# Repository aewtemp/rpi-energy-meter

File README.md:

# ----- W.I.P -----
# Raspberry-Pi Energy Meter

This Project is a combination of custom Hardware and Software, that will allow you to monitor your unique power situation in real time.

This project is derived from and inspired by the resources located at https://github.com/David00/rpi-power-monitor and https://learn.openenergymonitor.org.

## What does it do?
This code accompanies DIY circuitry that supports monitoring of up to 3 Phases with 6 current transformers each. The individual readings are then used in calculations to provide real data on consumption and generation, including the following key metrics:
* Voltage of every pahse
* Current on up to 6 channels per phase
* Power Factor
* Harmonics inspection through a built in snapshot/plotting mechanism.

The code takes thousands of samples per second, corrects for phase errors in the measurements, calculates the instantaneous power for the tens of thousands of sampled points, and uses the instantaneous power calculations to determine real power, apparent power, and power factor. This means the project is able to monitor any type of load, including reactive, capacitive, and resisitve loads.

## Where can I get it?
The whole Project is open sourced. You can order your PCBs via the Files provided in the [PCB Folder](PCB).  
You'll also find a [README](PCB/README.md) there which will provide more useful information.

## Installation & Documentation

### Ordering
#### Components for the PCB
Please take the respective components and their needed quantities from the [CSV](PCB/Production/RPiWattMeterHatv3.csv) inside the [PCB](PCB) folder.
#### The PCB
Just send the gerber files to the PCB Manufacturer of your choice.
If you provide the components file and the locations with the gerber files, you might be able to get the PCB nearly fully assembled.

### Preparing the Pi
#### System-Setup
You'll need a raspberry pi 3B with an installed operating system on it.
This has to be a 32-bit version, because the overlay file needed for the SPI-bus configuration won't work on 64-bit operating systems.
Currently supported operating systems are Debian (>11) and Ubuntu (>20.04)

* Copy the [overlay file (system_overlay/spi0-3cs-overlay.dtbo)](sytem_overlay/spi0-3cs-overlay.dtbo) into /boot/overlays  
* reboot

#### Installing the necessary software

### Installation and Configuration
#### Installation into the Cabinet
You will need 4 additional components to get the rpi-energy-meter up and running.
1. A DIN rail mountable power supply  
I had chosen this one: [MeanWell HDR-15-5](https://meanwell-ps.com/products/hdr-15-5)
2. 3 x fuse blocks, rated for 250V  
I had chosen this one: [XCELL UK5](https://www.uxcell.com/din-rail-mount-fuse-holder-terminal-blocks-screw-type-black-uk5-pack-p-1946790.html)
3. 3 x glass fuse, rated for 250V and 250mA  
I had chosen this one: [FUSE GLASS](https://www.digikey.de/en/products/detail/bel-fuse-inc/5HT-250-R/4439452)
4. Wires  
Ideally one would use black for the 230V live wires from and to the fuse holders, blue ones for the neutrals and red/black wires for the current transformer wires.  
The cross sections of the wires is:
    1. 230V/Neutal
        1. To the fuse blocks = 1.5mm² (15 AWG)
        1. From the fuse blocks = 0.5mm² (20 AWG)
        1. From the board (Neutral) = 0.5mm² (20 AWG)
    2. Current transformers
        1. Should be 0.5mm² or less (>= 20 AWG)

Select where you want your Voltage to be taken of for measurement. You'll have to select 3 sources, one for each phase.  
Connect wires from these points up to the fuse holders. From there you'll connect wires to the PCB - right where the imprint "DANGER HIGH VOLTAGE" is located.  
With the socket located at the bottom, left is phase 1, middle two are phase 2 and the right ones are phase 3.  
The Sequence is **N-L1-N-L2-N-L3**

#### Measuring required references
This step consists of some measurements which have to be taken in the cabinet and on the PCB. On the PCB are therefore some exposed through holes where you can take measurements from.

**!! BE CAREFUL WHEN TAKING MEASUREMENTS ON LIVE COMPONENTS !!**  

The following measurements have to be done:
* Voltages DC
    * 3.3V reference -> Exposed pads right next to the MCP3008 chips  
    Write down that value, it's needed later for the config.toml
    * Bias_V -> Exposed pads right above the Transformers on the PCB  
    Should be half of the reference Voltage
* Voltage AC
    * L{1,2,3}TRANS -> Exposed pads right next to the MCP3008 chips  
    Should read something from 2.0V to 2.2V RMS

#### Configuring the Energy-Meter

### Setting up a systemd service
* copy the [example systemd service file](examples/systemd/rpi-energy-meter.service) to /etc/systemd/system  
* modify the contents of /etc/systemd/systemd/rpi-energy-meter.service corresponding to your setup  
Most often you will need to adjust paths accordingly

### Expected results
#### Debug mode
The html charts generated by debug mode should look something like this  
[Phase 1](examples/debug/Phase_1.html?raw=true)  
[Phase 2](examples/debug/Phase_2.html?raw=true)  
[Phase 3](examples/debug/Phase_3.html?raw=true)

## Contributing

## Credits

---

## If you like what I did, you are welcome to leave me some support

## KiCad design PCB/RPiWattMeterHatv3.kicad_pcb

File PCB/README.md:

# ----- W.I.P -----
# Raspberry-Pi Energy Meter HAT

## What does it do?
This PCB is designed for measuring electrical current across three phases, with 6 individual channels per phase. Each channel represents a separate current path and uses current transformers (CTs) for sensing. The board uses 22 Ohm burden resistors for each CT channel.

Additionally, the board incorporates transformers to step down the mains voltage to a measurable level for voltage monitoring. **Caution:** This board operates with potentially dangerous voltages. There is **no touch protection**, and **improper handling may result in electric shock**.

This is a DIY project and comes with **no warranty or guarantee** of safety or performance. Use at your own risk.  
I personally have this setup running now for 2 years.

## Pictures of running setup

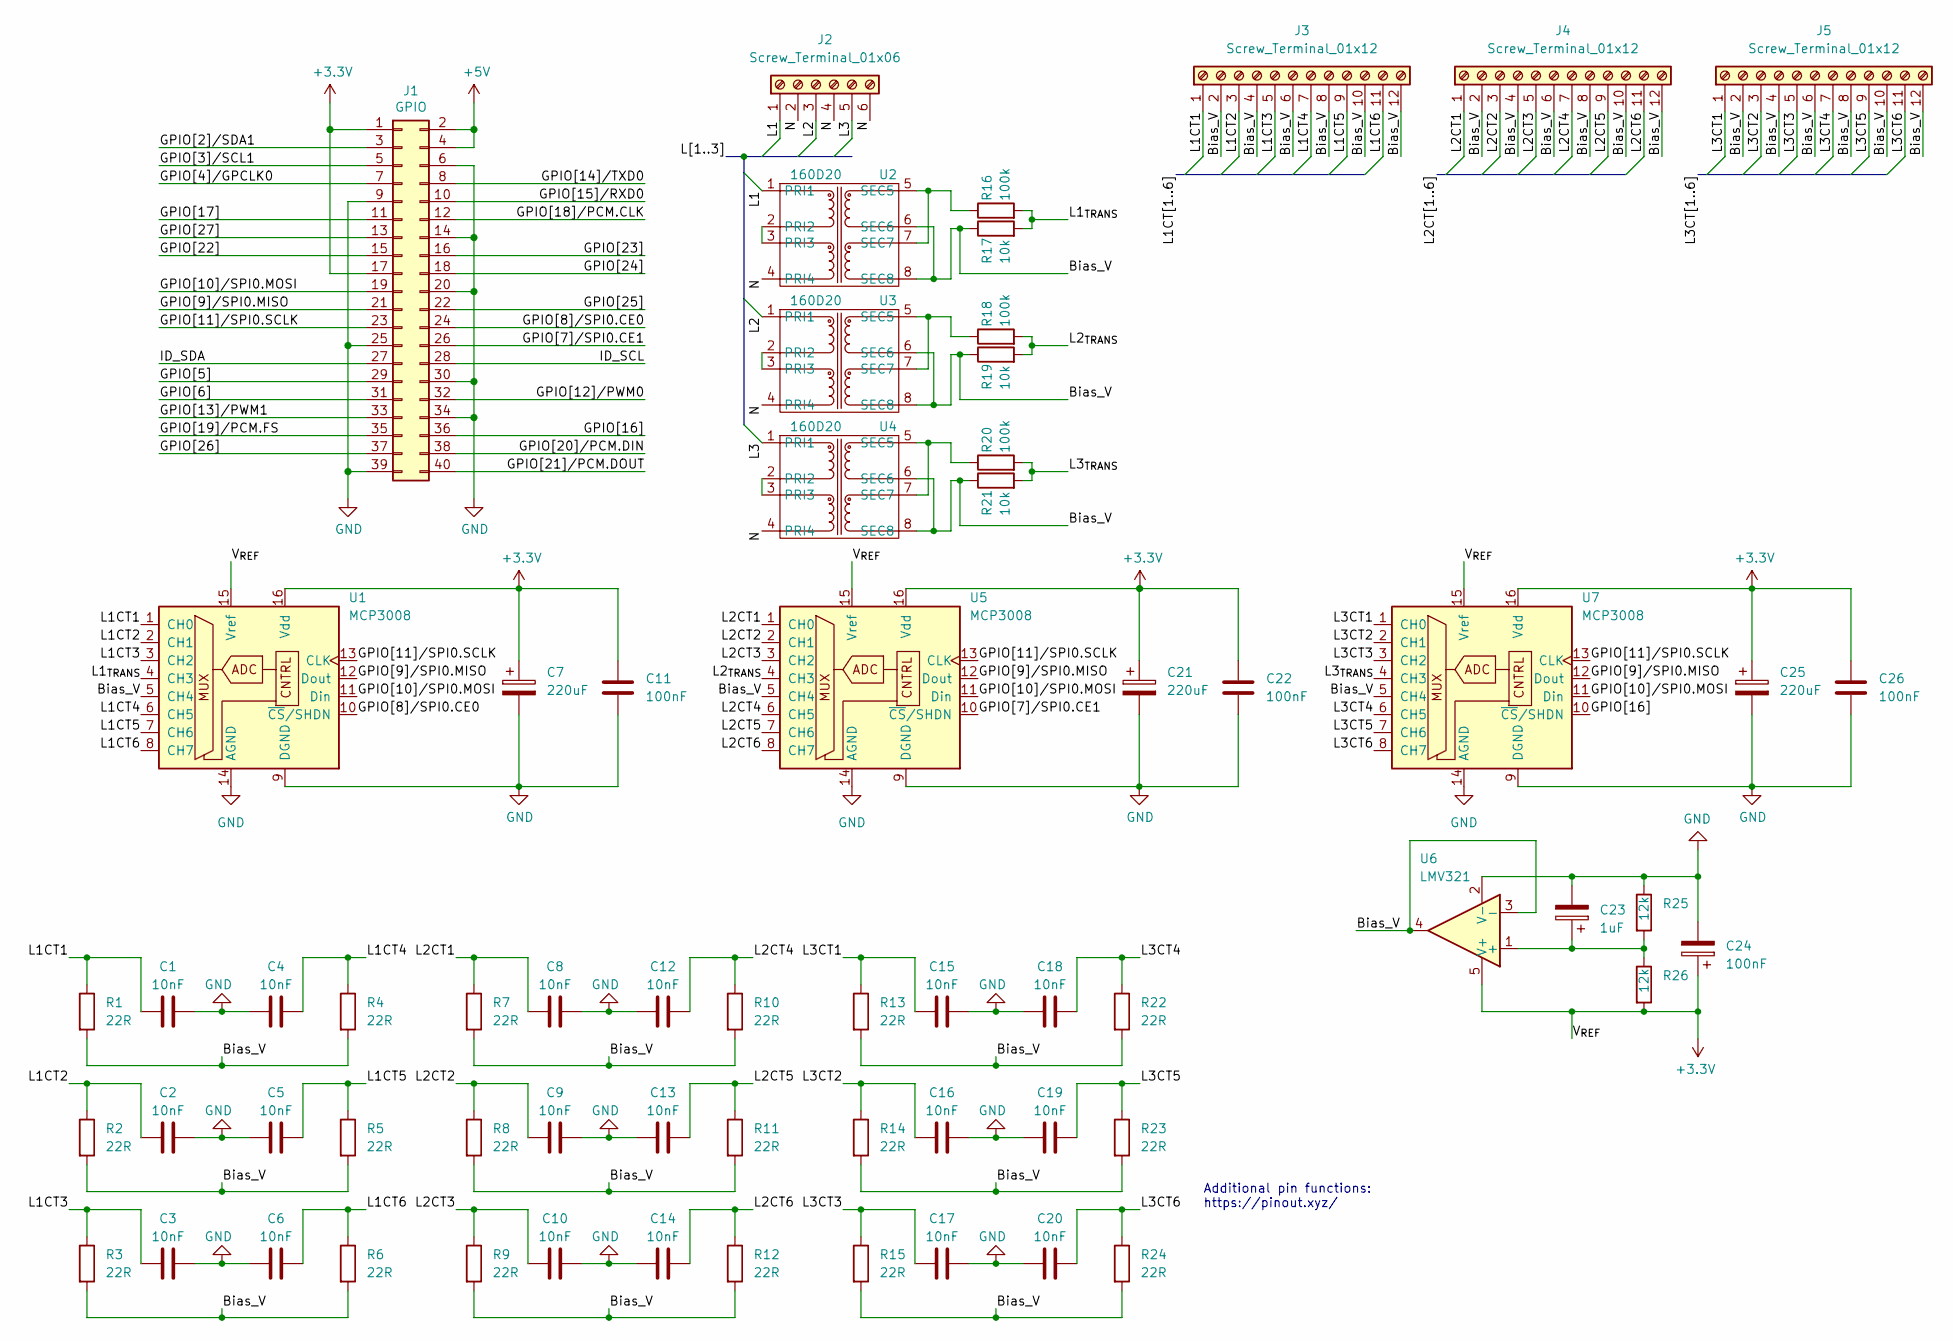
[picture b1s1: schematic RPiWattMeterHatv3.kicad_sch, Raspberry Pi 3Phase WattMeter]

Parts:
C1, C2, C3, C4, C5, C6, C8, C9, C10, C12, C13, C14, C15, C16, C17, C18, C19, C20: 10nF; C_1206_3216Metric_Pad1.33x1.80mm_HandSolder
C7, C21, C25: 220uF; CP_EIA-3216-12_Kemet-S_Pad1.58x1.35mm_HandSolder
C11, C22, C26: 100nF; C_1206_3216Metric_Pad1.33x1.80mm_HandSolder
C23: 1uF; C_1206_3216Metric_Pad1.33x1.80mm_HandSolder
C24: 100nF; CP_EIA-3216-12_Kemet-S_Pad1.58x1.35mm_HandSolder
J1: GPIO; PinSocket_2x20_P2.54mm_Vertical
J2: Screw_Terminal_01x06; PhoenixContact_1891108
J3, J4, J5: Screw_Terminal_01x12; PhoenixContact_PTSA 0,5_12-2,5-F
R1, R2, R3, R4, R5, R6, R7, R8, R9, R10, R11, R12, R13, R14, R15, R22, R23, R24: 22R; R_1206_3216Metric_Pad1.30x1.75mm_HandSolder
R16, R18, R20: 100k; R_1206_3216Metric_Pad1.30x1.75mm_HandSolder
R17, R19, R21: 10k; R_1206_3216Metric_Pad1.30x1.75mm_HandSolder
R25, R26: 12k; R_1206_3216Metric_Pad1.30x1.75mm_HandSolder
U1, U5, U7: MCP3008; DIP-16_W7.62mm_Socket
U2, U3, U4: 160D20; Hammond_160D20
U6: LMV321; SOT-23-5

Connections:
+3.3V: C7.1, C11.1, C21.1, C22.1, C24.1, C25.1, C26.1, J1.1, J1.17, R26.2, U1.15 (Vref), U1.16 (Vdd), U5.15 (Vref), U5.16 (Vdd), U6.5 (V+), U7.15 (Vref), U7.16 (Vdd)
+5V: J1.2, J1.4
/Bias_V: J3.2, J3.4, J3.6, J3.8, J3.10, J3.12, J4.2, J4.4, J4.6, J4.8, J4.10, J4.12, J5.2, J5.4, J5.6, J5.8, J5.10, J5.12, R1.2, R2.2, R3.2, R4.2, R5.2, R6.2, R7.2, R8.2, R9.2, R10.2, R11.2, R12.2, R13.2, R14.2, R15.2, R17.1, R19.1, R21.1, R22.2, R23.2, R24.2, U1.5 (CH4), U2.6 (SEC6), U2.8 (SEC8), U3.6 (SEC6), U3.8 (SEC8), U4.6 (SEC6), U4.8 (SEC8), U5.5 (CH4), U6.3 (-), U6.4, U7.5 (CH4)
/GPIO[2]/SDA1: J1.3
/GPIO[3]/SCL1: J1.5
/GPIO[4]/GPCLK0: J1.7
/GPIO[5]: J1.29
/GPIO[6]: J1.31
/GPIO[7]/SPI0.CE1: J1.26, U5.10 (~CS/SHDN)
/GPIO[8]/SPI0.CE0: J1.24, U1.10 (~CS/SHDN)
/GPIO[9]/SPI0.MISO: J1.21, U1.12 (Dout), U5.12 (Dout), U7.12 (Dout)
/GPIO[10]/SPI0.MOSI: J1.19, U1.11 (Din), U5.11 (Din), U7.11 (Din)
/GPIO[11]/SPI0.SCLK: J1.23, U1.13 (CLK), U5.13 (CLK), U7.13 (CLK)
/GPIO[12]/PWM0: J1.32
/GPIO[13]/PWM1: J1.33
/GPIO[14]/TXD0: J1.8
/GPIO[15]/RXD0: J1.10
/GPIO[16]: J1.36, U7.10 (~CS/SHDN)
/GPIO[17]: J1.11
/GPIO[18]/PCM.CLK: J1.12
/GPIO[19]/PCM.FS: J1.35
/GPIO[20]/PCM.DIN: J1.38
/GPIO[21]/PCM.DOUT: J1.40
/GPIO[22]: J1.15
/GPIO[23]: J1.16
/GPIO[24]: J1.18
/GPIO[25]: J1.22
/GPIO[26]: J1.37
/GPIO[27]: J1.13
/ID_SCL: J1.28
/ID_SDA: J1.27
/L1: J2.1, U2.1 (PRI1)
/L1CT1: C1.2, J3.1, R1.1, U1.1 (CH0)
/L1CT2: C2.2, J3.3, R2.1, U1.2 (CH1)
/L1CT3: C3.2, J3.5, R3.1, U1.3 (CH2)
/L1CT4: C4.1, J3.7, R4.1, U1.6 (CH5)
/L1CT5: C5.1, J3.9, R5.1, U1.7 (CH6)
/L1CT6: C6.1, J3.11, R6.1, U1.8 (CH7)
/L1_{TRANS}: R16.2, R17.2, U1.4 (CH3)
/L2: J2.3, U3.1 (PRI1)
/L2CT1: C8.2, J4.1, R7.1, U5.1 (CH0)
/L2CT2: C9.2, J4.3, R8.1, U5.2 (CH1)
/L2CT3: C10.2, J4.5, R9.1, U5.3 (CH2)
/L2CT4: C12.1, J4.7, R10.1, U5.6 (CH5)
/L2CT5: C13.1, J4.9, R11.1, U5.7 (CH6)
/L2CT6: C14.1, J4.11, R12.1, U5.8 (CH7)
/L2_{TRANS}: R18.2, R19.2, U5.4 (CH3)
/L3: J2.5, U4.1 (PRI1)
/L3CT1: C15.2, J5.1, R13.1, U7.1 (CH0)
/L3CT2: C16.2, J5.3, R14.1, U7.2 (CH1)
/L3CT3: C17.2, J5.5, R15.1, U7.3 (CH2)
/L3CT4: C18.1, J5.7, R22.1, U7.6 (CH5)
/L3CT5: C19.1, J5.9, R23.1, U7.7 (CH6)
/L3CT6: C20.1, J5.11, R24.1, U7.8 (CH7)
/L3_{TRANS}: R20.2, R21.2, U7.4 (CH3)
/N: J2.2, J2.4, J2.6, U2.4 (PRI4), U3.4 (PRI4), U4.4 (PRI4)
GND: C1.1, C2.1, C3.1, C4.2, C5.2, C6.2, C7.2, C8.1, C9.1, C10.1, C11.2, C12.2, C13.2, C14.2, C15.1, C16.1, C17.1, C18.2, C19.2, C20.2, C21.2, C22.2, C23.2, C24.2, C25.2, C26.2, J1.6, J1.9, J1.14, J1.20, J1.25, J1.30, J1.34, J1.39, R25.1, U1.9 (DGND), U1.14 (AGND), U5.9 (DGND), U5.14 (AGND), U6.2 (V-), U7.9 (DGND), U7.14 (AGND)
unnamed: C23.1, R25.2, R26.1, U6.1 (+)
unnamed: R16.1, U2.5 (SEC5), U2.7 (SEC7)
unnamed: R18.1, U3.5 (SEC5), U3.7 (SEC7)
unnamed: R20.1, U4.5 (SEC5), U4.7 (SEC7)
unnamed: U2.2 (PRI2), U2.3 (PRI3)
unnamed: U3.2 (PRI2), U3.3 (PRI3)
unnamed: U4.2 (PRI2), U4.3 (PRI3)

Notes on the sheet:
Additional pin functions: https://pinout.xyz/

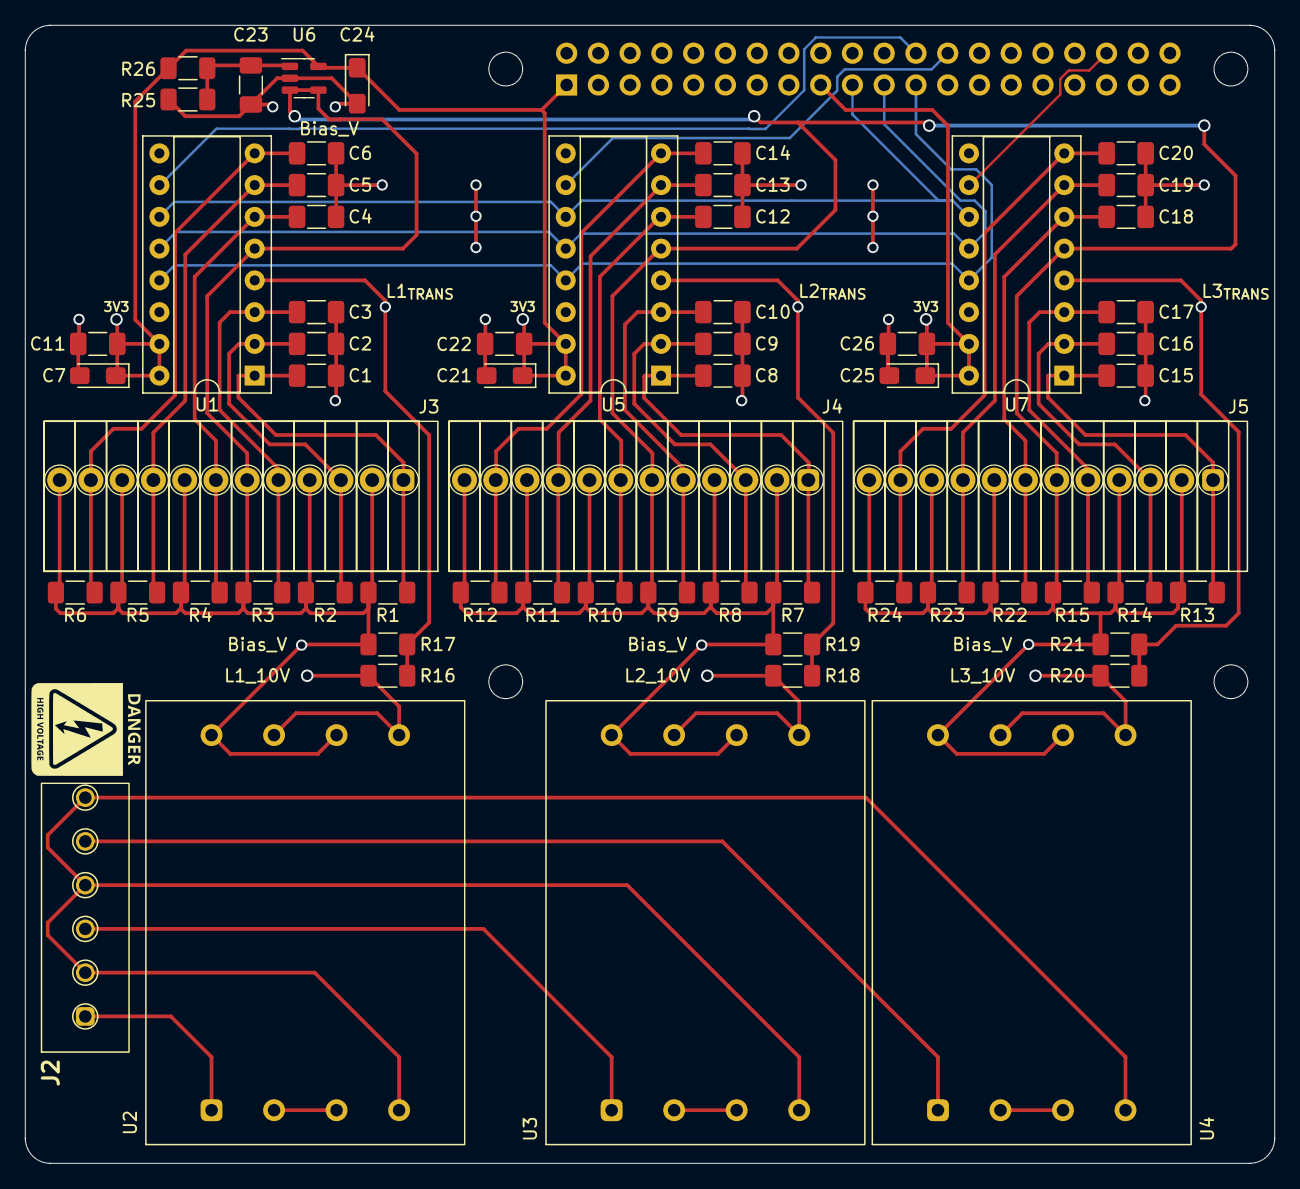
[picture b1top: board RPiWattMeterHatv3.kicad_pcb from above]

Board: 2 copper layers, 99.9 x 91.0 mm, 68 parts (1 on the bottom side), 42 nets.

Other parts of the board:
MH1, MH2, MH3, MH4: MountingHole_2.7mm_M2.5

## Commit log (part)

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2025-04-14 Pushed PCB data, some images and updated READMEs.
2025-04-14 embed images in the README
2025-04-15 renamed images
2025-04-16 fixes and updates to logging, configuration and samples
2025-04-16 still work in progress...
2025-04-16 updated example config
2025-04-16 vscode launch.json for debbung purposes
2025-04-16 Updated requirements.
2025-04-16 running state. Now cleaning.
2025-04-16 better filenames
2025-04-16 KWH saved
2025-04-16 reducing duplicated code
2025-04-16 cleaning comments
2025-04-16 static path for c mcp library
2025-04-16 implemented cutoff
2025-04-17 typos
2025-04-17 pyproject.toml
2025-04-17 correct path for final installation
2025-04-17 missing arguments
2025-04-17 changes should be made consistently
2025-04-17 Old KWH should be lower to trigger reset...
2025-04-17 updated config.py and config.toml.example
2025-04-17 Some examples ffor a systemd service file and some example measurements from debug mode
2025-04-18 removed KiCad Backups
2025-04-18 .gitignore
